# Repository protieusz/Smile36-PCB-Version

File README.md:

# Smile36-PCB-Version

I accept any tips or donations of a cup of coffee to help keep me motivate but you don't have to if you don't want to. Thanks. https://ko-fi.com/protieusz

Update Aug 25, 2025. Got sponsored by  for PETG print for my new case design of Smile 36 "Chatacabra" from Monster Hunter Wilds.

PCBWay:
For all you 3D printing needs, PCBWay got all types of materials for your printing needs. Ranging from PLA to Resin, https://www.pcbway.com/rapid-prototyping/3d-printing/ for more info. Quality check by PCWay was very good. Their engineer will notify you if you have thin walls in your design and if you want to "risk" printing it. Printed items arrived with quality packing to ensure no damage or scratches during transport. Well worth it. Printing of my PETG for top and bottom case took around 1 day and ship out on the same day via UPS. The item was shipped out on Friday and arrived to my home address on the next Monday. Print quality is very good, rigid and no scratches. Thank you PCBWay!

Smile 36 Chatacabra Pics:
Chatacabra image was borrowed from https://cults3d.com/en/3d-model/jewelry/chatacabra-keychain-mh-wilds-chatacabra-llavero-monster-hunter by NOGARDLABS. Please support & buy his keychain STL files for 3D print. The design was cleaned up very nicely so that it was easily incorporated into my custom keeb design. The design was modified to have the keychain hole removed.

The acrylic paint doesn't go smooth on the PETG material but still looks good.

My PLA 3D Printed Version Using My Bambu A1:

Update: July 9, 2023. Got featured in https://kbd.news/Smile36-2056.html

Update: July 7, 2023

A special thank you to  for sponsoring my Rev 8 of the Smile 36 GRIN layout keyboard that has every thing working compared to Rev 1 which has the issue of the rows not working.  

Initial order arrived with easily scratch matte black silk screen on all 5 pcbs.  Functionality wise, the pcb work with no issues, continuity check outs. I reported the issues to the representative for my sponsorship and he was kind enough to replace the whole order with a new color pcb of my choice and so I picked purple.  Around 1 week ish, my pcb reprints enter production and was shipped by DHL free of charge to my address.  The results were awesome.  The purple pcbs were bright in color, shiny and the outline cuts were smooth with no sharp edges.  Ordering the pcbs from PCBWay was very easy.  You just specify the pcb dimensions, the pcb thickness, the color you want and leave most of the settings to default.  After you uploaded the gerber files, the status will be in review and an engineer will review your designs and goes into production when it is a passed.  Shipping wise, it has very many options ranging for express to budget shipping.  Prices are in USDs. Here is the direct link for ordering from PCBWay. [(https://www.pcbway.com/project/shareproject/Smile_36_GRIN_Layout_Custom_Keyboard_1b3776b9.html)].  Rev 8 gerber files will be upload to Github soon or you can download from the PCBWay link.

The following are the pictures of my brand new Smile 36 Rev 8 with no more handwiring fixes.

# Disclaimer

This work is a non-commercial fan creation of custom keyboard case and PCB in the shape of SpongeBob & Patrick Star, Chatacabra from the Monster Hunter Wilds & SpongeBob SquarePants series. It is made out of love and respect for the Monster Hunter Wilds & SpongeBob SquarePants series. All rights to Monster Hunter Wilds & SpongeBob SquarePants and related content are owned by Capcom & Nickelodeon and its associated companies. The images, names, storylines and other elements of Chatacabra & SpongeBob SquarePants used in this work are the property of their respective copyright holders. Unauthorized commercial use is strictly prohibited. The Chatacabra & SpongeBob SquarePants and Patrick Star case files will NOT be made public to copyright issues and will be use for private only.

Please print and use the open sourced files at your own risk.

# Pictures

Update: October 8, 2024. Patrick Star Smile 36 case inspired by Patrick from SpongeBob SquarePants.

Some hiccup accident while soldering the mcu. Mcu was soldered on the wrong side. Tried hot plate and hot air and the damn mcu pcb will not come off. All the mcu components came off.
So then I gave up on desoldering the mcu and soldered a new mcu on the correct side and it works. There is hope if you have accidentally "F" up on the mcu. My top and bottom case was created
to accomodate 2 mcu soldered on top and bottom side of the Smile36 PCB. Just make sure you desolder all the components on the mcu PCB and use a yellow tape to prevent any future shorts.

Update: October 4, 2024. Smile 36 case inspired by SpongeBob SquarePants. Featured on [KBDnews](https://kbd.news/Behind-the-scenes-176-2493.html)

Final Smile 36 with no case yet. Note: Case has not been tested yet. As a matter of fact, use everything here at your own risk! No support given.

Bottom side using another spare pcb as bottom plate.

Cross section, no mods yet.

Different angle shots.

Key testing passed.

MCU prep for soldering.

Diode soldering.

Unpackaging pics.

Converted From Handwire To PCB Using EasyEDA

Current Rev 5 pcb has fixed the issues of Rev 1 and also by adding multi layer pads, thru holes for the mcu solder pads, larger pads for easier soldering, added more screw holes in the middle of the pcb so less flexy and stability.  However the Rev 5 pcbs will be untested since I do not have the funds to do a re-print.  Hence the are for public and print, use for at your own risks!  Don't come to me and bitch about it.  It is what it is. No support will be given. Having said that the Rev 5 pcb should work.  Auto routed and no DRC errors. Good luck and have fun.

Added a case STEP file that was used for handwire version. Please modify the STEP file to match the pcb version.

Rev 6 top:

Rev 6 bottom:

Rev 1: My very 1st pcb design, forgot that smd pads only works on 1 layer and not both layers so all my rows are not connected, so had to salvaged it by handwired it to the mcu and it works.

Close up on the handwire fix

Preview

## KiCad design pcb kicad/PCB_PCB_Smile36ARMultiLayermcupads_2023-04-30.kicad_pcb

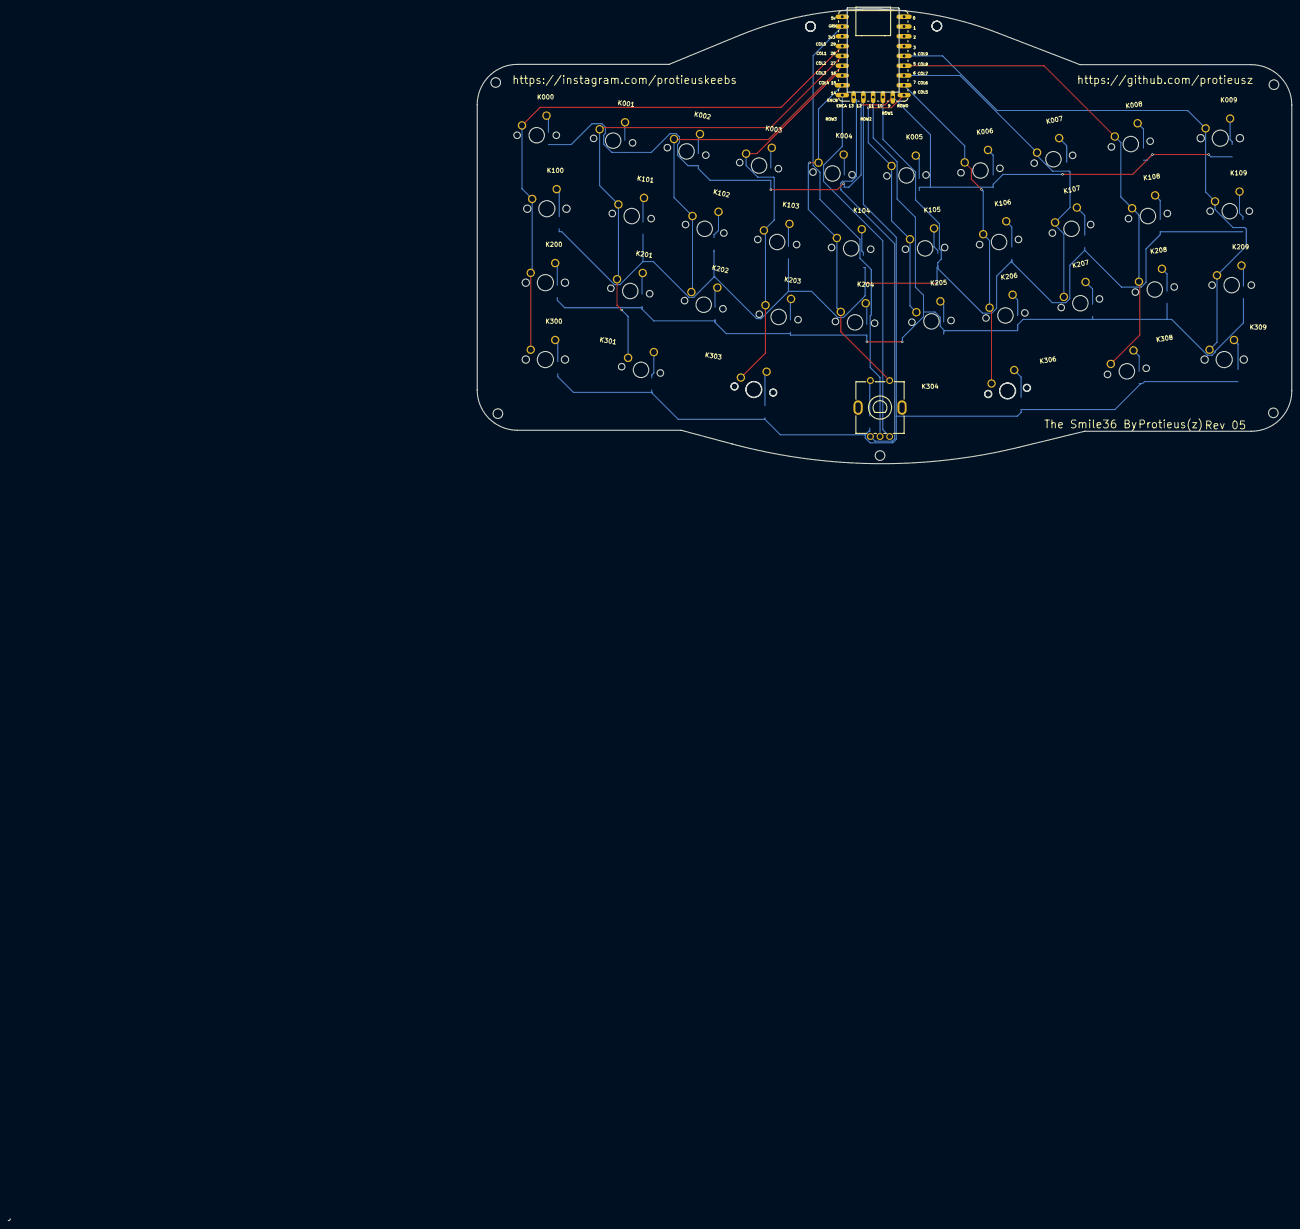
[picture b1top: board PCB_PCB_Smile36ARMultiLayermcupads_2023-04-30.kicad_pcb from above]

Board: 2 copper layers, 211.2 x 117.8 mm, 75 parts (0 on the bottom side), 54 nets.

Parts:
D000, D001, D002, D003, D004, D005, D006, D007, D008, D009, D100, D101, D102, D103, D104, D105, D106, D107, D108, D109, D200, D201, D202, D203, D204, D205, D206, D207, D208, D209, D300, D301, D303, D304, D306, D308, D309: DIODE-SOD123
K000, K001, K002, K003, K004, K005, K006, K007, K008, K101, K102, K103, K104, K105, K106, K107, K108, K109, K201, K202, K203, K204, K205, K206, K207, K208, K209, K301, K308: 100; CHERRY_MX_100_MILLMAX
K009, K100, K200, K300, K309: 125; CHERRY_MX_125_MILLMAX
K303, K306: 175; CHERRY_MX_175_MILLMAX
K304: PEC11R-4015F-S0024; SW-TH_PEC11R-4XXXF-SXXXX
U1: RP2040-ZERO_WAVESHARE - with GPIO; RP2040-ZERO_WAVESHARE- W/ GPIO

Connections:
COL0: K000.2, K100.MX2, K200.MX2, K300.MX2, U1.19
COL1: K001.2, K101.2, K201.2, K301.2, U1.18
COL2: K002.2, K102.2, K202.2, U1.17
COL3: K003.2, K103.2, K203.2, K303.MX2, U1.16
COL4: K004.2, K104.2, K204.2, K304.2, U1.15
COL5: K005.2, K105.2, K205.2, U1.8
COL6: K006.2, K106.2, K206.2, K306.MX2, U1.7
COL7: K007.2, K107.2, K207.2, U1.6
COL8: K008.2, K108.2, K208.2, K308.2, U1.5
COL9: K009.MX2, K109.2, K209.2, K309.MX2, U1.4
D000_A: D000.A, K000.1
D003_A: D003.A, K003.1
D005_A: D005.A, K005.1
D007_A: D007.A, K007.1
D009_A: D009.A, K009.MX1
D101_A: D101.A, K101.1
D102_A: D102.A, K102.1
D104_A: D104.A, K104.1
D106_A: D106.A, K106.1
D108_A: D108.A, K108.1
D201_A: D201.A, K201.1
D202_A: D202.A, K202.1
D204_A: D204.A, K204.1
D206_A: D206.A, K206.1
D208_A: D208.A, K208.1
D300_A: D300.A, K300.MX1
D308_A: D308.A, K308.1
D309_A: D309.A, K309.MX1
ENCA: K304.A, U1.13
ENCB: K304.B, U1.14
GND: K304.C, U1.21
K001_1: D001.A, K001.1
K002_1: D002.A, K002.1
K004_1: D004.A, K004.1
K006_1: D006.A, K006.1
K008_1: D008.A, K008.1
K100_MX1: D100.A, K100.MX1
K103_1: D103.A, K103.1
K105_1: D105.A, K105.1
K107_1: D107.A, K107.1
K109_1: D109.A, K109.1
K200_MX1: D200.A, K200.MX1
K203_1: D203.A, K203.1
K205_1: D205.A, K205.1
K207_1: D207.A, K207.1
K209_1: D209.A, K209.1
K301_1: D301.A, K301.1
K303_MX1: D303.A, K303.MX1
K304_1: D304.A, K304.1
K306_MX1: D306.A, K306.MX1
ROW0: D000.C, D001.C, D002.C, D003.C, D004.C, D005.C, D006.C, D007.C, D008.C, D009.C, U1.9
ROW1: D100.C, D101.C, D102.C, D103.C, D104.C, D105.C, D106.C, D107.C, D108.C, D109.C, U1.10
ROW2: D200.C, D201.C, D202.C, D203.C, D204.C, D205.C, D206.C, D207.C, D208.C, D209.C, U1.11
ROW3: D300.C, D301.C, D303.C, D304.C, D306.C, D308.C, D309.C, U1.12

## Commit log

2023-04-03 Update pcb pic
2023-04-27 Update with pics and readme blurp
2023-04-27 Upload gerbers rev 5
2023-04-27 Upload QMK firmware source code
2023-04-30 Add kicad pcb conversion and schematic
2023-04-30 Add KLE to make ppl's life easier
2023-05-01 Need to add logo
2023-05-01 Logo added
2023-05-03 Update with Rev 6 pcb rendered pics
2023-05-03 Add Rev07 Smaller Logo
2023-05-09 Add untested case STEP file
2023-05-11 Add untested full case & switch plate pcb
2023-06-05 Kirtan's keymap
2023-06-13 Typo edit
2023-06-14 Create top mount pcb case
2023-07-08 Update README.md
    Added PCBWay sponsorship and Rev 8 pics
2023-07-08 Update README.md
    Grammer
2023-07-08 Update README.md
    Grammar
2023-07-08 Update README.md
    Spelling
2023-07-09 Rev8 Gerbers
2023-07-09 Rev 8 Case
2023-07-09 Update README.md
    Add case warning
2024-10-03 Smile36 Case STEP
2024-10-07 VIAL firmware By HA HA HA
